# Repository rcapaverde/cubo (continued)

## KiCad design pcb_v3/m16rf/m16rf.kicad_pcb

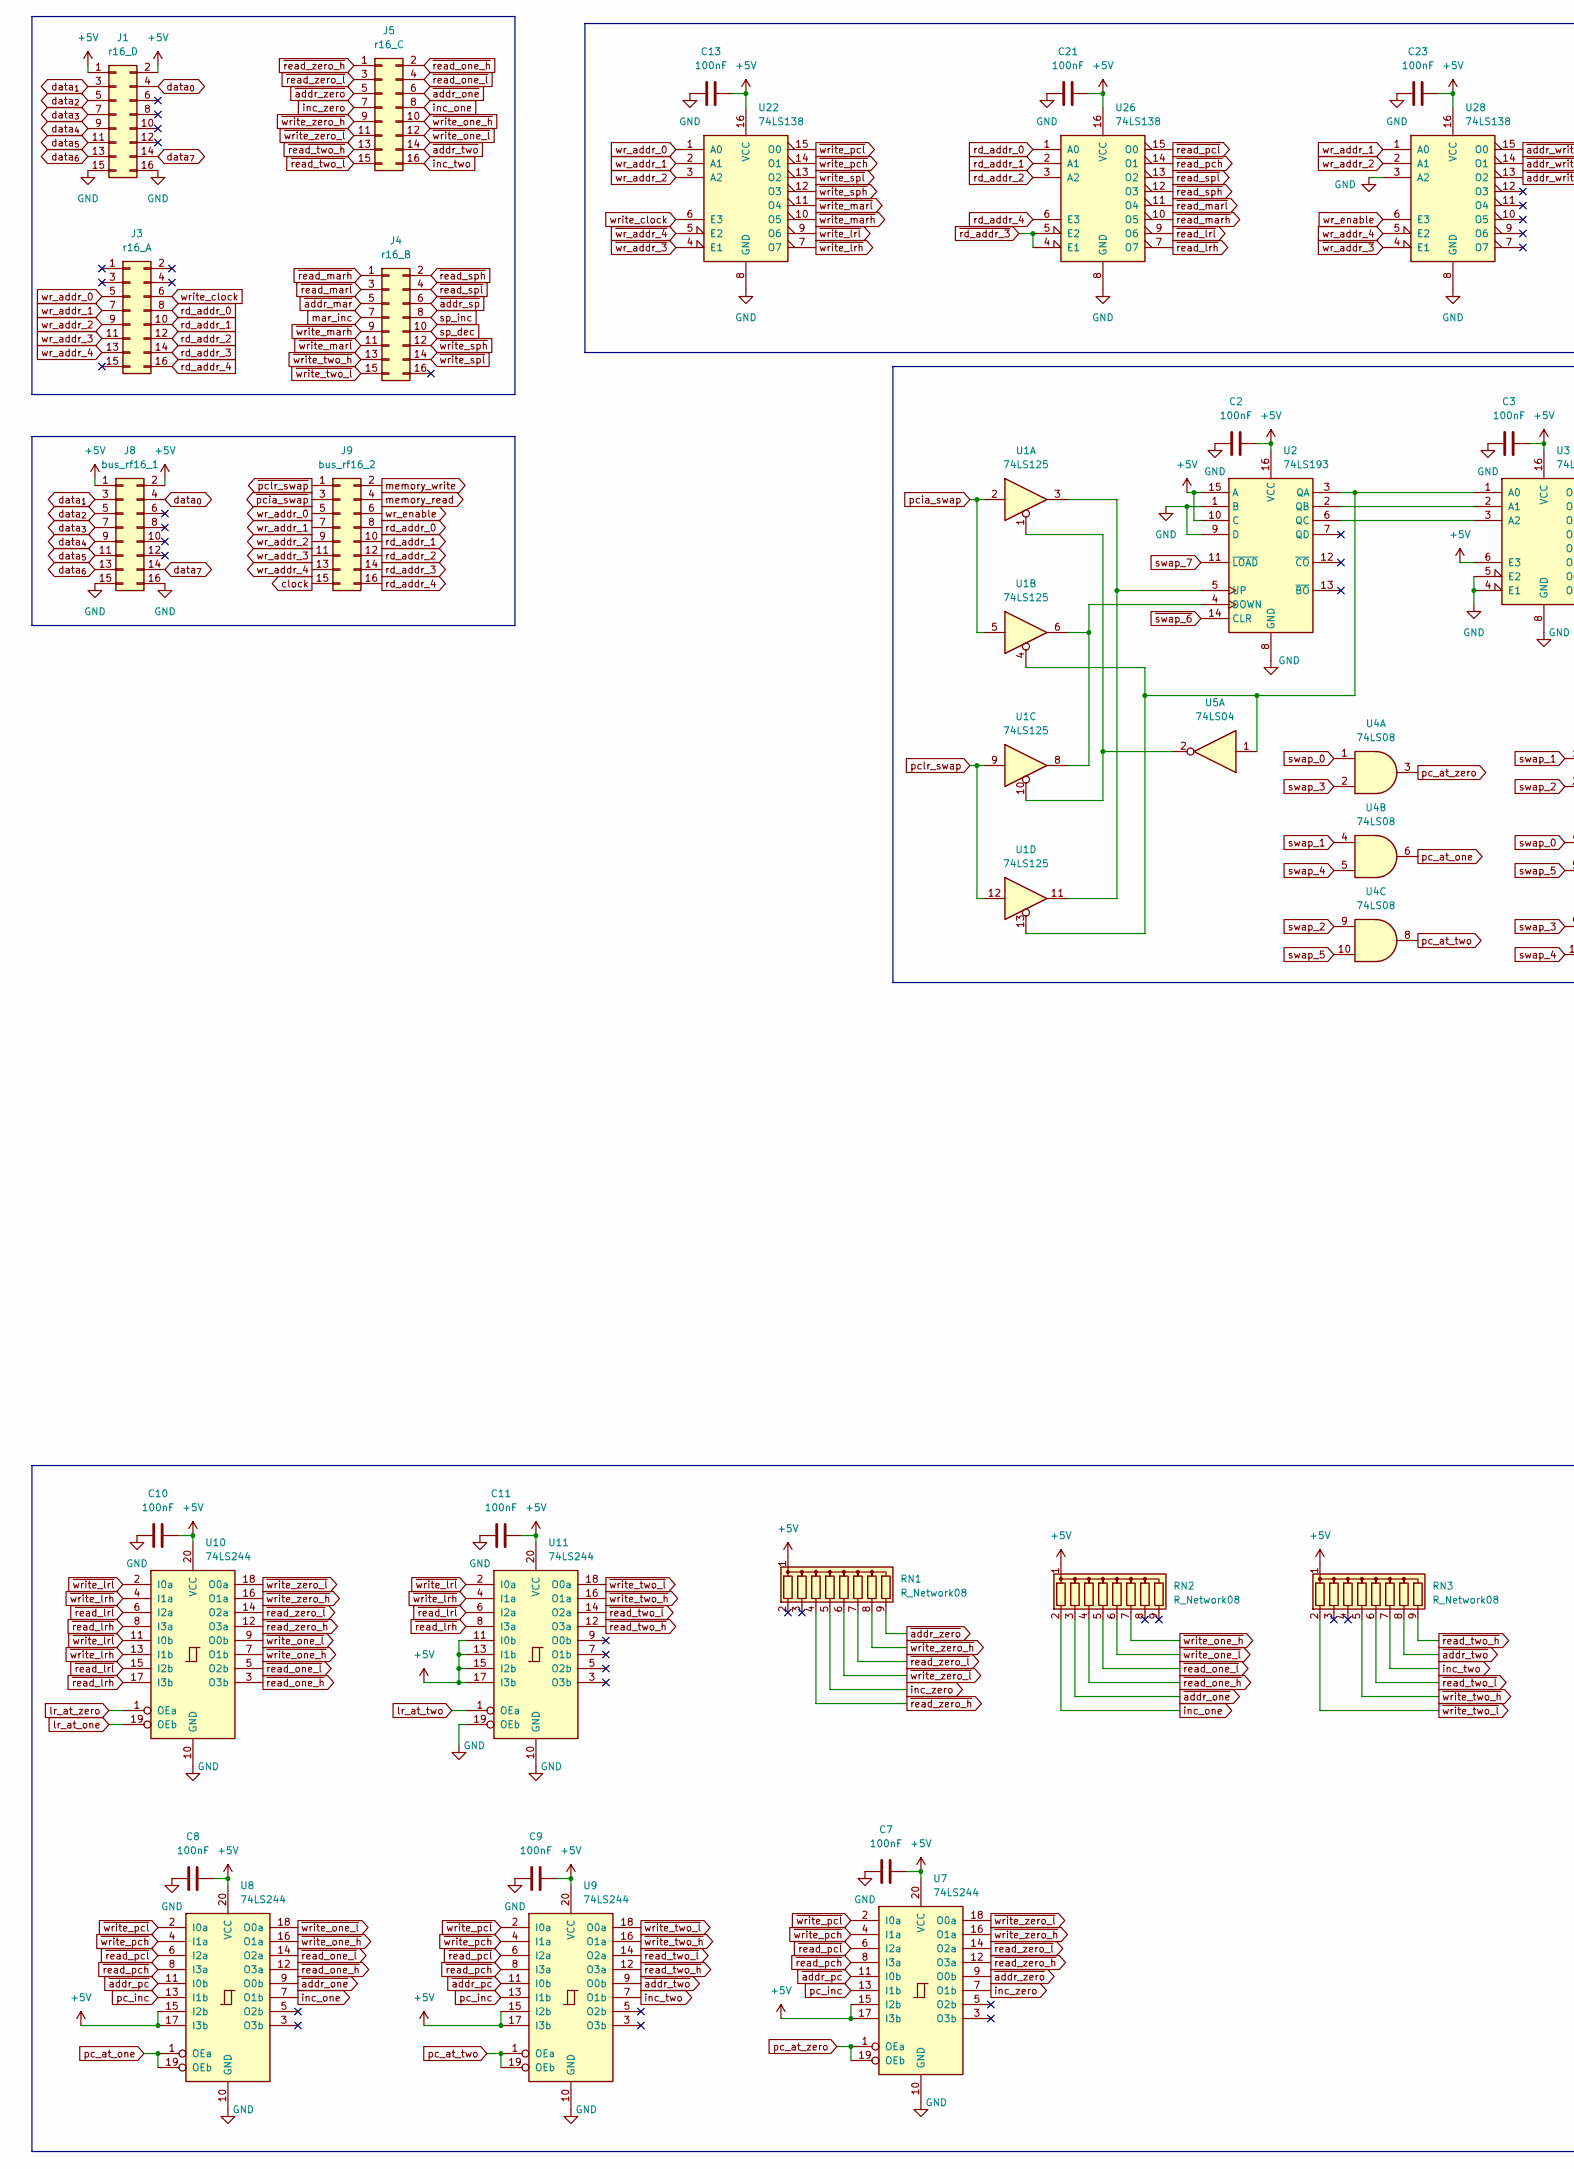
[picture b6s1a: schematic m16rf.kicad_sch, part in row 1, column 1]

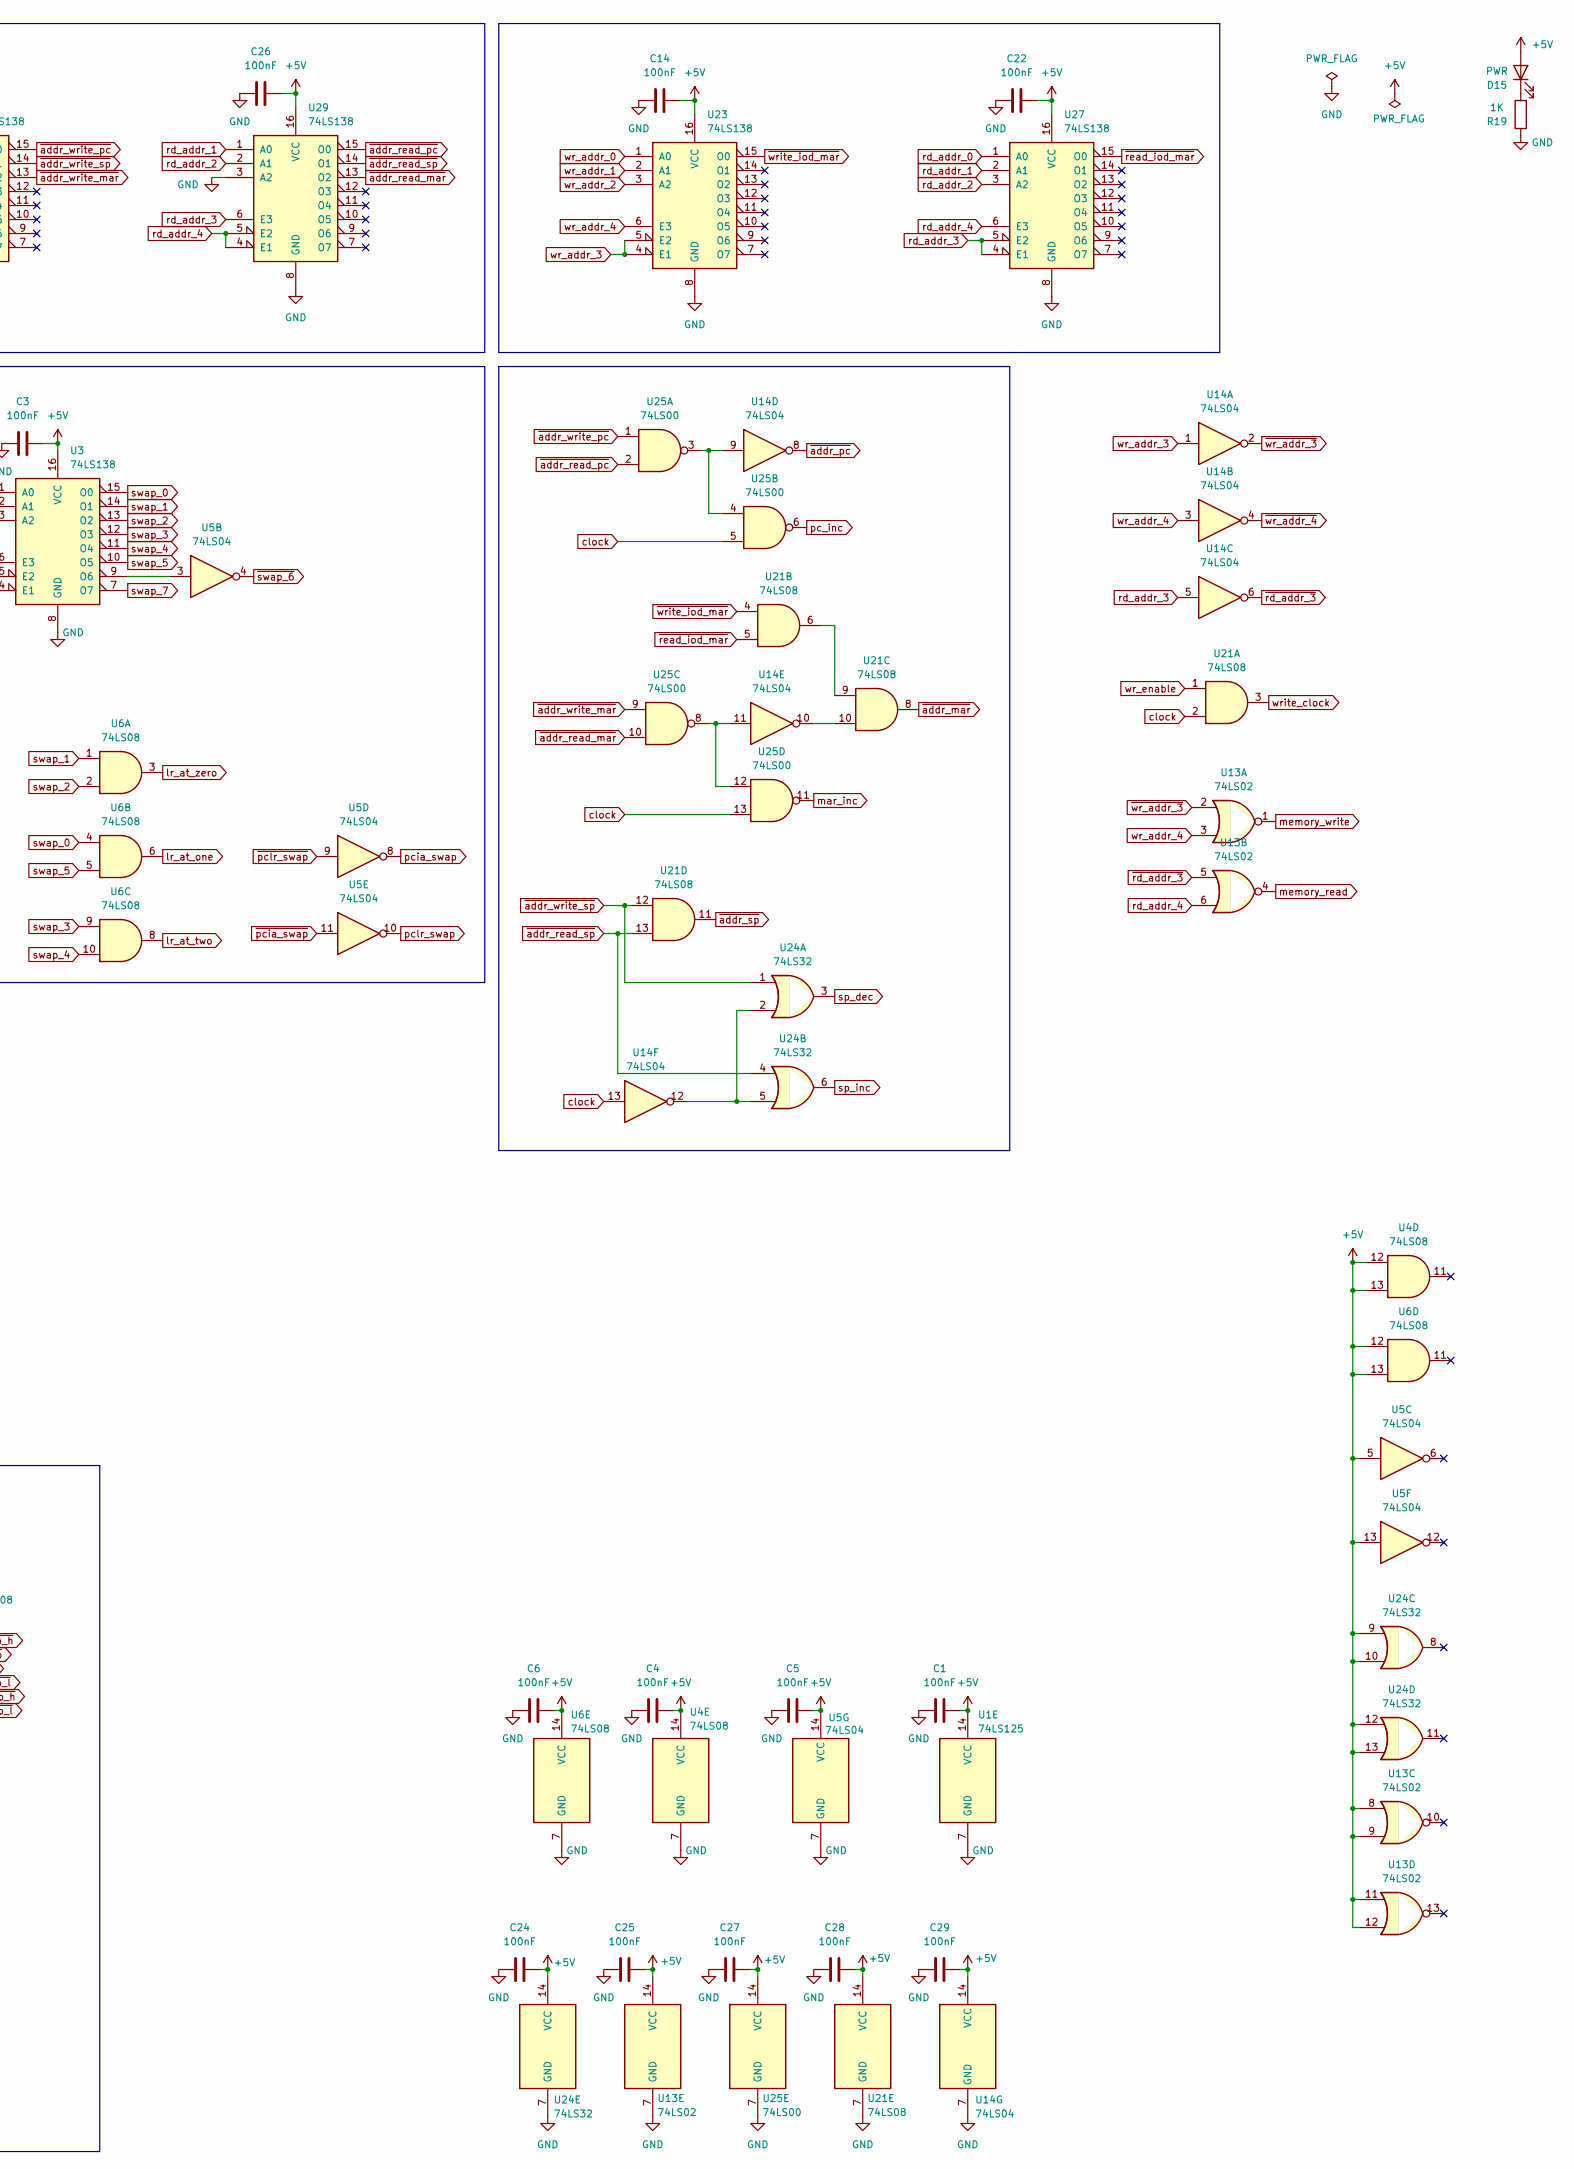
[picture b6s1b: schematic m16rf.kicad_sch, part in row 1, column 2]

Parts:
C1, C2, C3, C4, C5, C6, C7, C8, C9, C10, C11, C13, C14, C21, C22, C23, C24, C25, C26, C27, C28, C29: 100nF; C_Disc_D5.1mm_W3.2mm_P5.00mm
D15: PWR; LED_D5.0mm
J1: r16_D; conector 02x08
J3: r16_A; conector 02x08
J4: r16_B; conector 02x08
J5: r16_C; conector 02x08
J8: bus_rf16_1; conector 02x08
J9: bus_rf16_2; conector 02x08
R19: 1K; R_Axial_DIN0207_L6.3mm_D2.5mm_P7.62mm_Horizontal
RN1, RN2, RN3: R_Network08; R_Array_SIP9
U1: 74LS125; DIP-14_W7.62mm
U2: 74LS193; DIP-16_W7.62mm
U3, U22, U23, U26, U27, U28, U29: 74LS138; DIP-16_W7.62mm
U4, U6, U21: 74LS08; DIP-14_W7.62mm
U5, U14: 74LS04; DIP-14_W7.62mm
U7, U8, U9, U10, U11: 74LS244; DIP-20_W7.62mm
U13: 74LS02; DIP-14_W7.62mm
U24: 74LS32; DIP-14_W7.62mm
U25: 74LS00; DIP-14_W7.62mm

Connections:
+5V: C1.2, C2.2, C3.2, C4.2, C5.2, C6.2, C7.2, C8.2, C9.2, C10.2, C11.2, C13.2, C14.2, C21.2, C22.2, C23.2, C24.2, C25.2, C26.2, C27.2, C28.2, C29.2, D15.2 (A), J1.1, J1.2, J8.1, J8.2, RN1.1 (common), RN2.1 (common), RN3.1 (common), U1.14 (VCC), U2.10 (C), U2.15 (A), U2.16 (VCC), U3.6 (E3), U3.16 (VCC), U4.12, U4.13, U4.14 (VCC), U5.5, U5.13, U5.14 (VCC), U6.12, U6.13, U6.14 (VCC), U7.15 (I2b), U7.17 (I3b), U7.20 (VCC), U8.15 (I2b), U8.17 (I3b), U8.20 (VCC), U9.15 (I2b), U9.17 (I3b), U9.20 (VCC), U10.20 (VCC), U11.11 (I0b), U11.13 (I1b), U11.15 (I2b), U11.17 (I3b), U11.20 (VCC), U13.8, U13.9, U13.11, U13.12, U13.14 (VCC), U14.14 (VCC), U21.14 (VCC), U22.16 (VCC), U23.16 (VCC), U24.9, U24.10, U24.12, U24.13, U24.14 (VCC), U25.14 (VCC), U26.16 (VCC), U27.16 (VCC), U28.16 (VCC), U29.16 (VCC)
GND: C1.1, C2.1, C3.1, C4.1, C5.1, C6.1, C7.1, C8.1, C9.1, C10.1, C11.1, C13.1, C14.1, C21.1, C22.1, C23.1, C24.1, C25.1, C26.1, C27.1, C28.1, C29.1, J1.15, J1.16, J8.15, J8.16, R19.1, U1.7 (GND), U2.1 (B), U2.8 (GND), U2.9 (D), U3.4 (E1), U3.5 (E2), U3.8 (GND), U4.7 (GND), U5.7 (GND), U6.7 (GND), U7.10 (GND), U8.10 (GND), U9.10 (GND), U10.10 (GND), U11.10 (GND), U11.19 (OEb), U13.7 (GND), U14.7 (GND), U21.7 (GND), U22.8 (GND), U23.8 (GND), U24.7 (GND), U25.7 (GND), U26.8 (GND), U27.8 (GND), U28.3 (A2), U28.8 (GND), U29.3 (A2), U29.8 (GND)
unnamed: D15.1 (K), R19.2
unnamed: U1.1, U1.10, U5.2
unnamed: U1.6, U1.8, U2.4 (DOWN)
unnamed: U1.4, U1.13, U2.3 (QA), U3.1 (A0), U5.1
unnamed: U2.2 (QB), U3.2 (A1)
unnamed: U2.6 (QC), U3.3 (A2)
unnamed: U1.3, U1.11, U2.5 (UP)
unnamed: U3.9 (O6), U5.3
unnamed: U14.9, U25.3, U25.4
unnamed: U14.10, U21.10
unnamed: U14.11, U25.8, U25.12
unnamed: U14.12, U24.2, U24.5
unnamed: U21.6, U21.9
clock: J9.15, U14.13, U21.2, U25.5, U25.13
data_{0}: J1.4, J8.4
data_{1}: J1.3, J8.3
data_{2}: J1.5, J8.5
data_{3}: J1.7, J8.7
data_{4}: J1.9, J8.9
data_{5}: J1.11, J8.11
data_{6}: J1.13, J8.13
data_{7}: J1.14, J8.14
inc_one: J5.8, RN2.2 (R1), U8.7 (O1b)
inc_two: J5.16, RN3.7 (R6), U9.7 (O1b)
inc_zero: J5.7, RN1.5 (R4), U7.7 (O1b)
lr_at_one: U6.6, U10.19 (OEb)
lr_at_two: U6.8, U11.1 (OEa)
lr_at_zero: U6.3, U10.1 (OEa)
mar_inc: J4.7, U25.11
memory_read: J9.4, U13.4
memory_write: J9.2, U13.1
pc_at_one: U4.6, U8.1 (OEa), U8.19 (OEb)
pc_at_two: U4.8, U9.1 (OEa), U9.19 (OEb)
pc_at_zero: U4.3, U7.1 (OEa), U7.19 (OEb)
pc_inc: U7.13 (I1b), U8.13 (I1b), U9.13 (I1b), U25.6
pcia_swap: U1.2, U1.5, U5.8
pclr_swap: U1.9, U1.12, U5.10
rd_addr_0: J3.8, J9.8, U26.1 (A0), U27.1 (A0)
rd_addr_1: J3.10, J9.10, U26.2 (A1), U27.2 (A1), U29.1 (A0)
rd_addr_2: J3.12, J9.12, U26.3 (A2), U27.3 (A2), U29.2 (A1)
rd_addr_3: J3.14, J9.14, U14.5, U27.4 (E1), U27.5 (E2), U29.6 (E3)
rd_addr_4: J3.16, J9.16, U13.6, U26.6 (E3), U27.6 (E3), U29.4 (E1), U29.5 (E2)
sp_dec: J4.10, U24.3
sp_inc: J4.8, U24.6
swap_0: U3.15 (O0), U4.1, U6.4
swap_1: U3.14 (O1), U4.4, U6.1
swap_2: U3.13 (O2), U4.9, U6.2
swap_3: U3.12 (O3), U4.2, U6.9
swap_4: U3.11 (O4), U4.5, U6.10
swap_5: U3.10 (O5), U4.10, U6.5
swap_7: U2.11 (~LOAD), U3.7 (O7)
wr_addr_0: J3.5, J9.5, U22.1 (A0), U23.1 (A0)
wr_addr_1: J3.7, J9.7, U22.2 (A1), U23.2 (A1), U28.1 (A0)
wr_addr_2: J3.9, J9.9, U22.3 (A2), U23.3 (A2), U28.2 (A1)
wr_addr_3: J3.11, J9.11, U14.1, U23.4 (E1), U23.5 (E2)
wr_addr_4: J3.13, J9.13, U13.3, U14.3, U23.6 (E3), U28.5 (E2)
wr_enable: J9.6, U21.1, U28.6 (E3)
write_clock: J3.6, U21.3, U22.6 (E3)
~addr_mar: J4.5, U21.8
~addr_one: J5.6, RN2.3 (R2), U8.9 (O0b)
~addr_pc: U7.11 (I0b), U8.11 (I0b), U9.11 (I0b), U14.8
~addr_read_mar: U25.10, U29.13 (O2)
~addr_read_pc: U25.2, U29.15 (O0)
~addr_read_sp: U21.13, U24.4, U29.14 (O1)
~addr_sp: J4.6, U21.11
~addr_two: J5.14, RN3.8 (R7), U9.9 (O0b)
~addr_write_mar: U25.9, U28.13 (O2)
~addr_write_pc: U25.1, U28.15 (O0)
~addr_write_sp: U21.12, U24.1, U28.14 (O1)
~addr_zero: J5.5, RN1.9 (R8), U7.9 (O0b)
~pcia_swap: J9.3, U5.11
~pclr_swap: J9.1, U5.9
~rd_addr_3: U13.5, U14.6, U26.4 (E1), U26.5 (E2)
~read_iod_mar: U21.5, U27.15 (O0)
~read_lrh: U10.8 (I3a), U10.17 (I3b), U11.8 (I3a), U26.7 (O7)
~read_lrl: U10.6 (I2a), U10.15 (I2b), U11.6 (I2a), U26.9 (O6)
~read_marh: J4.1, U26.10 (O5)
~read_marl: J4.3, U26.11 (O4)
~read_one_h: J5.2, RN2.4 (R3), U8.12 (O3a), U10.3 (O3b)
~read_one_l: J5.4, RN2.5 (R4), U8.14 (O2a), U10.5 (O2b)
~read_pch: U7.8 (I3a), U8.8 (I3a), U9.8 (I3a), U26.14 (O1)
~read_pcl: U7.6 (I2a), U8.6 (I2a), U9.6 (I2a), U26.15 (O0)
~read_sph: J4.2, U26.12 (O3)
~read_spl: J4.4, U26.13 (O2)
~read_two_h: J5.13, RN3.9 (R8), U9.12 (O3a), U11.12 (O3a)
~read_two_l: J5.15, RN3.6 (R5), U9.14 (O2a), U11.14 (O2a)
~read_zero_h: J5.1, RN1.4 (R3), U7.12 (O3a), U10.12 (O3a)
~read_zero_l: J5.3, RN1.7 (R6), U7.14 (O2a), U10.14 (O2a)
~swap_6: U2.14 (CLR), U5.4
~wr_addr_3: U13.2, U14.2, U22.4 (E1), U28.4 (E1)
~wr_addr_4: U14.4, U22.5 (E2)
~write_iod_mar: U21.4, U23.15 (O0)
~write_lrh: U10.4 (I1a), U10.13 (I1b), U11.4 (I1a), U22.7 (O7)
~write_lrl: U10.2 (I0a), U10.11 (I0b), U11.2 (I0a), U22.9 (O6)
~write_marh: J4.9, U22.10 (O5)
~write_marl: J4.11, U22.11 (O4)
~write_one_h: J5.10, RN2.7 (R6), U8.16 (O1a), U10.7 (O1b)
~write_one_l: J5.12, RN2.6 (R5), U8.18 (O0a), U10.9 (O0b)
~write_pch: U7.4 (I1a), U8.4 (I1a), U9.4 (I1a), U22.14 (O1)
~write_pcl: U7.2 (I0a), U8.2 (I0a), U9.2 (I0a), U22.15 (O0)
~write_sph: J4.12, U22.12 (O3)
~write_spl: J4.14, U22.13 (O2)
~write_two_h: J4.13, RN3.5 (R4), U9.16 (O1a), U11.16 (O1a)
~write_two_l: J4.15, RN3.2 (R1), U9.18 (O0a), U11.18 (O0a)
~write_zero_h: J5.9, RN1.8 (R7), U7.16 (O1a), U10.16 (O1a)
~write_zero_l: J5.11, RN1.6 (R5), U7.18 (O0a), U10.18 (O0a)

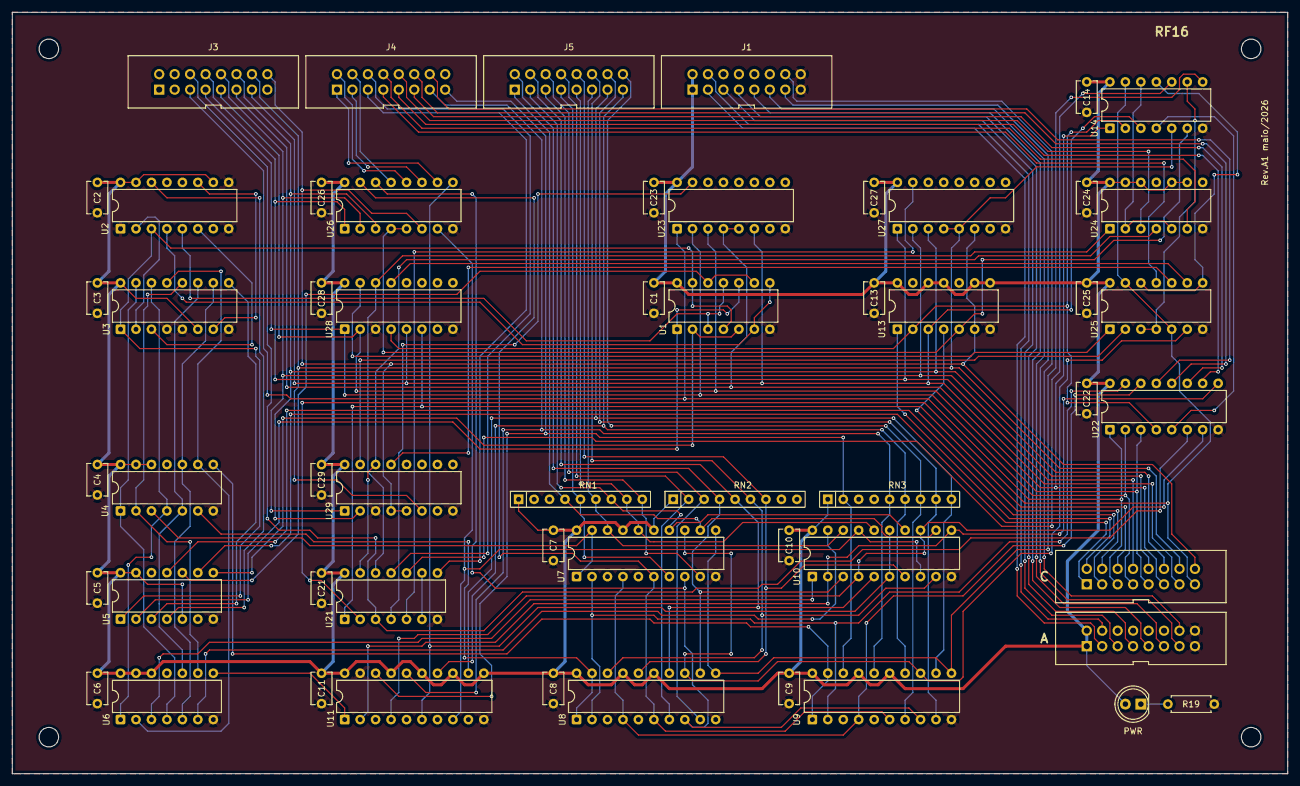
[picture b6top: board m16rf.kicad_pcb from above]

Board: 2 copper layers, 209.5 x 125.1 mm, 55 parts (0 on the bottom side), 108 nets.

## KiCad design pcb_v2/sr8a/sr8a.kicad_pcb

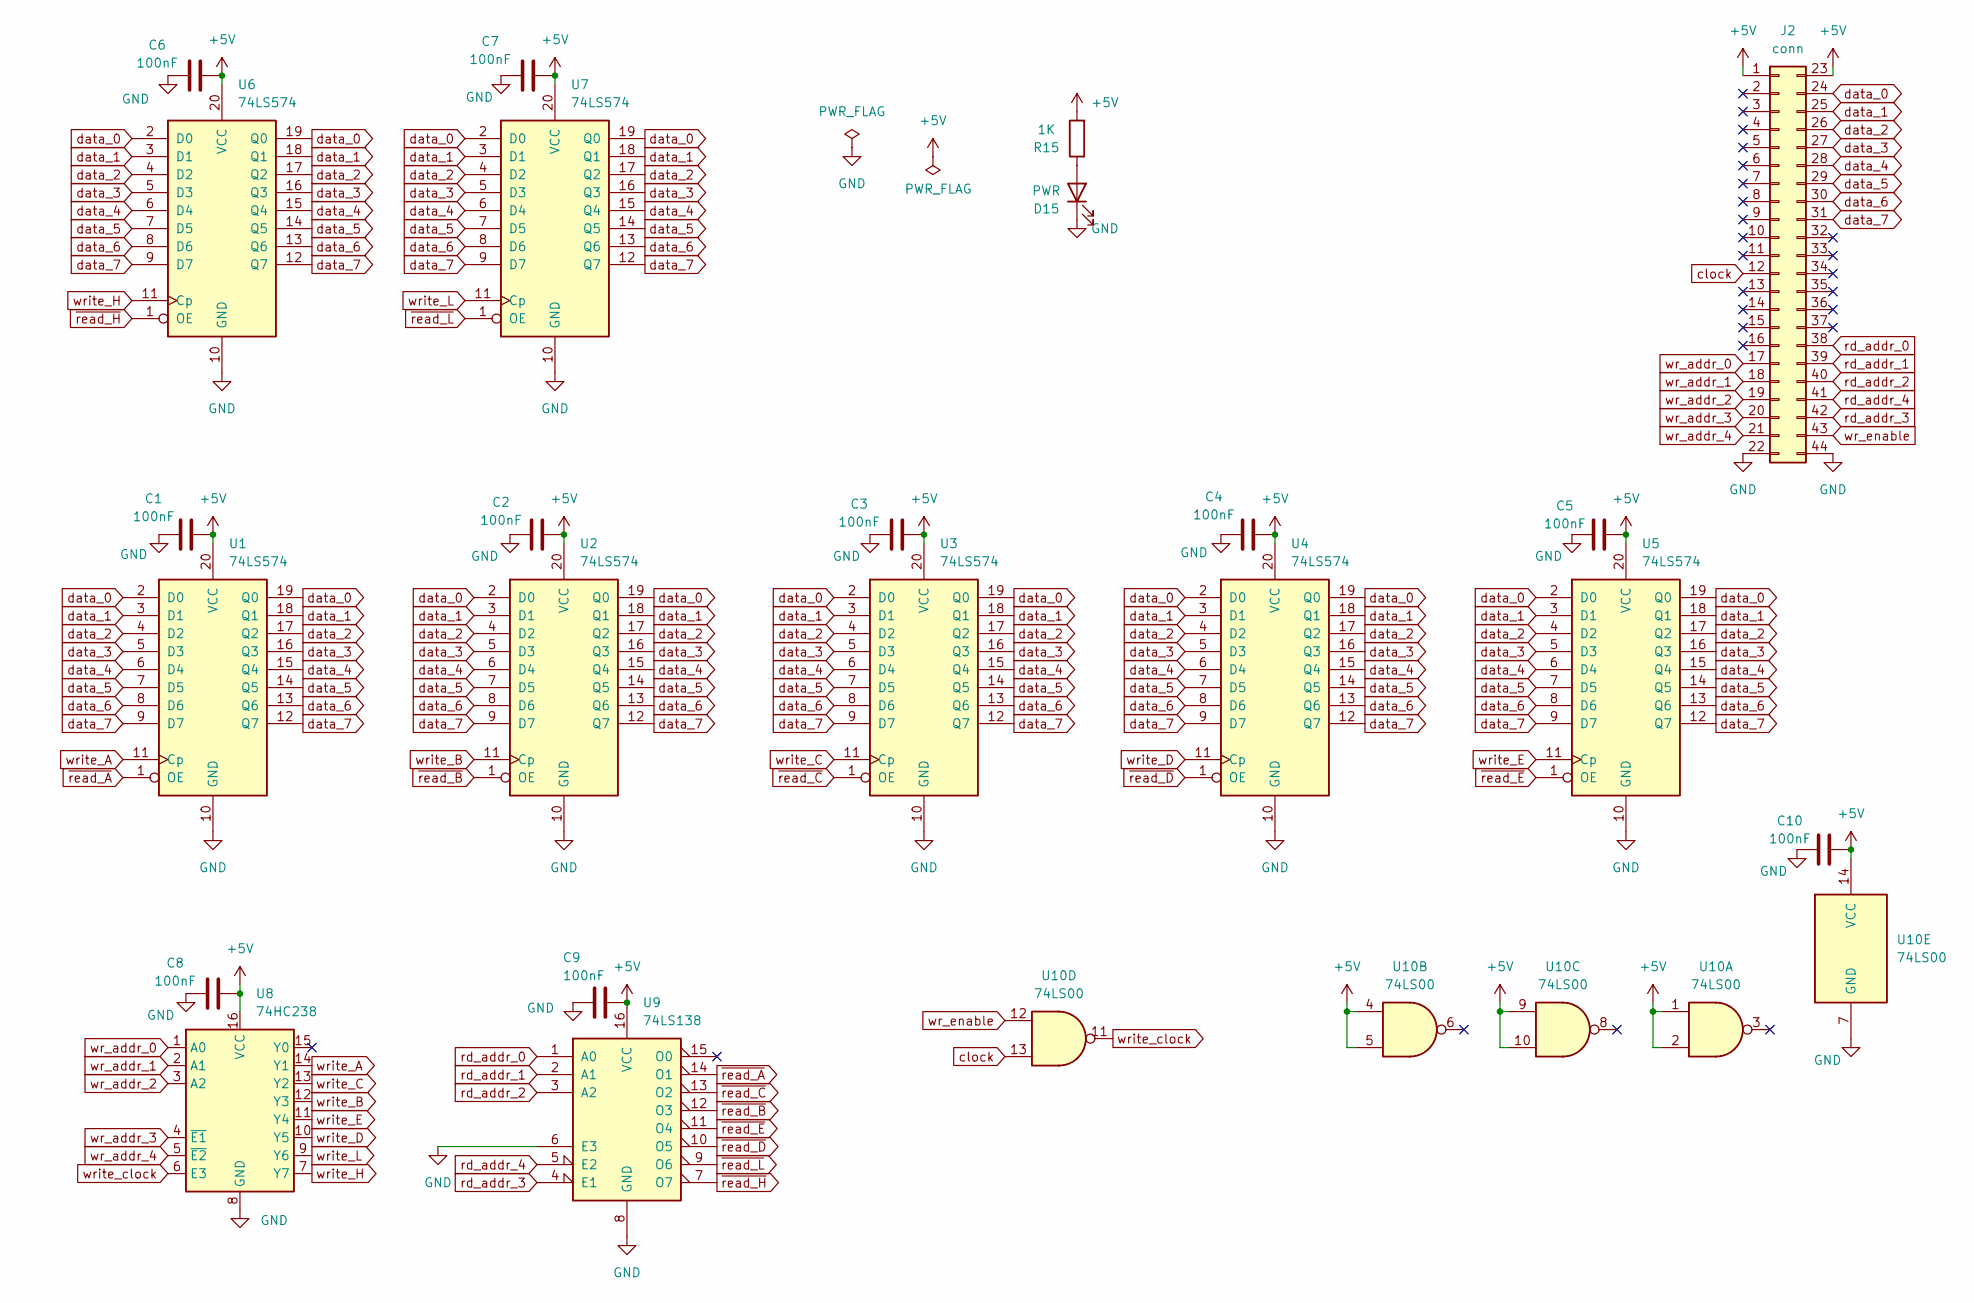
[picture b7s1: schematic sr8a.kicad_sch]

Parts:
C1, C2, C3, C4, C5, C6, C7, C8, C9, C10: 100nF; C_Disc_D5.1mm_W3.2mm_P5.00mm
D15: PWR; LED_D5.0mm
J2: conn; edge-connector-44
R15: 1K; R_Axial_DIN0207_L6.3mm_D2.5mm_P7.62mm_Horizontal
U1, U2, U3, U4, U5, U6, U7: 74LS574; DIP-20_W7.62mm
U8: 74HC238; DIP-16_W7.62mm
U9: 74LS138; DIP-16_W7.62mm
U10: 74LS00; DIP-14_W7.62mm

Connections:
+5V: C1.2, C2.2, C3.2, C4.2, C5.2, C6.2, C7.2, C8.2, C9.2, C10.2, J2.1, J2.23, R15.2, U1.20 (VCC), U2.20 (VCC), U3.20 (VCC), U4.20 (VCC), U5.20 (VCC), U6.20 (VCC), U7.20 (VCC), U8.16 (VCC), U9.16 (VCC), U10.1, U10.2, U10.4, U10.5, U10.9, U10.10, U10.14 (VCC)
GND: C1.1, C2.1, C3.1, C4.1, C5.1, C6.1, C7.1, C8.1, C9.1, C10.1, D15.1 (K), J2.22, J2.44, U1.10 (GND), U2.10 (GND), U3.10 (GND), U4.10 (GND), U5.10 (GND), U6.10 (GND), U7.10 (GND), U8.8 (GND), U9.6 (E3), U9.8 (GND), U10.7 (GND)
unnamed: D15.2 (A), R15.1
clock: J2.12, U10.13
data_0: J2.24, U1.2 (D0), U1.19 (Q0), U2.2 (D0), U2.19 (Q0), U3.2 (D0), U3.19 (Q0), U4.2 (D0), U4.19 (Q0), U5.2 (D0), U5.19 (Q0), U6.2 (D0), U6.19 (Q0), U7.2 (D0), U7.19 (Q0)
data_1: J2.25, U1.3 (D1), U1.18 (Q1), U2.3 (D1), U2.18 (Q1), U3.3 (D1), U3.18 (Q1), U4.3 (D1), U4.18 (Q1), U5.3 (D1), U5.18 (Q1), U6.3 (D1), U6.18 (Q1), U7.3 (D1), U7.18 (Q1)
data_2: J2.26, U1.4 (D2), U1.17 (Q2), U2.4 (D2), U2.17 (Q2), U3.4 (D2), U3.17 (Q2), U4.4 (D2), U4.17 (Q2), U5.4 (D2), U5.17 (Q2), U6.4 (D2), U6.17 (Q2), U7.4 (D2), U7.17 (Q2)
data_3: J2.27, U1.5 (D3), U1.16 (Q3), U2.5 (D3), U2.16 (Q3), U3.5 (D3), U3.16 (Q3), U4.5 (D3), U4.16 (Q3), U5.5 (D3), U5.16 (Q3), U6.5 (D3), U6.16 (Q3), U7.5 (D3), U7.16 (Q3)
data_4: J2.28, U1.6 (D4), U1.15 (Q4), U2.6 (D4), U2.15 (Q4), U3.6 (D4), U3.15 (Q4), U4.6 (D4), U4.15 (Q4), U5.6 (D4), U5.15 (Q4), U6.6 (D4), U6.15 (Q4), U7.6 (D4), U7.15 (Q4)
data_5: J2.29, U1.7 (D5), U1.14 (Q5), U2.7 (D5), U2.14 (Q5), U3.7 (D5), U3.14 (Q5), U4.7 (D5), U4.14 (Q5), U5.7 (D5), U5.14 (Q5), U6.7 (D5), U6.14 (Q5), U7.7 (D5), U7.14 (Q5)
data_6: J2.30, U1.8 (D6), U1.13 (Q6), U2.8 (D6), U2.13 (Q6), U3.8 (D6), U3.13 (Q6), U4.8 (D6), U4.13 (Q6), U5.8 (D6), U5.13 (Q6), U6.8 (D6), U6.13 (Q6), U7.8 (D6), U7.13 (Q6)
data_7: J2.31, U1.9 (D7), U1.12 (Q7), U2.9 (D7), U2.12 (Q7), U3.9 (D7), U3.12 (Q7), U4.9 (D7), U4.12 (Q7), U5.9 (D7), U5.12 (Q7), U6.9 (D7), U6.12 (Q7), U7.9 (D7), U7.12 (Q7)
rd_addr_0: J2.38, U9.1 (A0)
rd_addr_1: J2.39, U9.2 (A1)
rd_addr_2: J2.40, U9.3 (A2)
rd_addr_3: J2.42, U9.4 (E1)
rd_addr_4: J2.41, U9.5 (E2)
wr_addr_0: J2.17, U8.1 (A0)
wr_addr_1: J2.18, U8.2 (A1)
wr_addr_2: J2.19, U8.3 (A2)
wr_addr_3: J2.20, U8.4 (~E1)
wr_addr_4: J2.21, U8.5 (~E2)
wr_enable: J2.43, U10.12
write_A: U1.11 (Cp), U8.14 (Y1)
write_B: U2.11 (Cp), U8.12 (Y3)
write_C: U3.11 (Cp), U8.13 (Y2)
write_D: U4.11 (Cp), U8.10 (Y5)
write_E: U5.11 (Cp), U8.11 (Y4)
write_H: U6.11 (Cp), U8.7 (Y7)
write_L: U7.11 (Cp), U8.9 (Y6)
write_clock: U8.6 (E3), U10.11
~read_A: U1.1 (OE), U9.14 (O1)
~read_B: U2.1 (OE), U9.12 (O3)
~read_C: U3.1 (OE), U9.13 (O2)
~read_D: U4.1 (OE), U9.10 (O5)
~read_E: U5.1 (OE), U9.11 (O4)
~read_H: U6.1 (OE), U9.7 (O7)
~read_L: U7.1 (OE), U9.9 (O6)

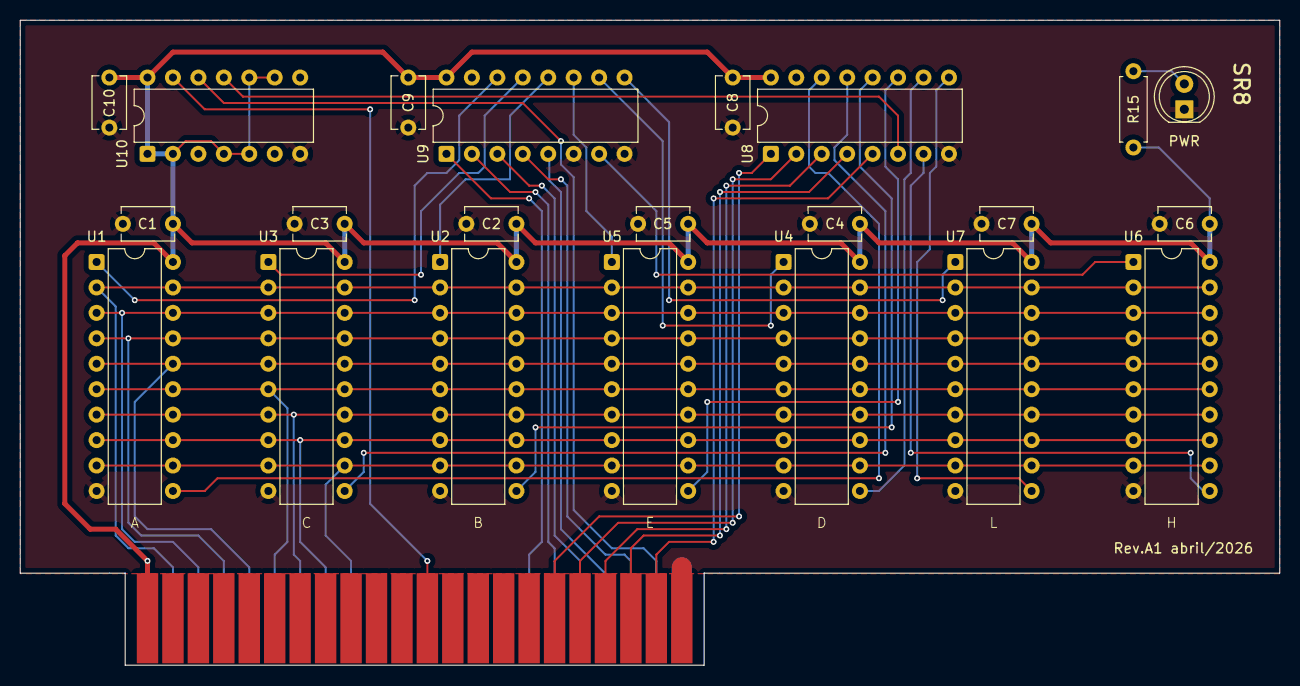
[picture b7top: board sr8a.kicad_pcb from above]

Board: 2 copper layers, 125.7 x 64.4 mm, 23 parts (0 on the bottom side), 38 nets.

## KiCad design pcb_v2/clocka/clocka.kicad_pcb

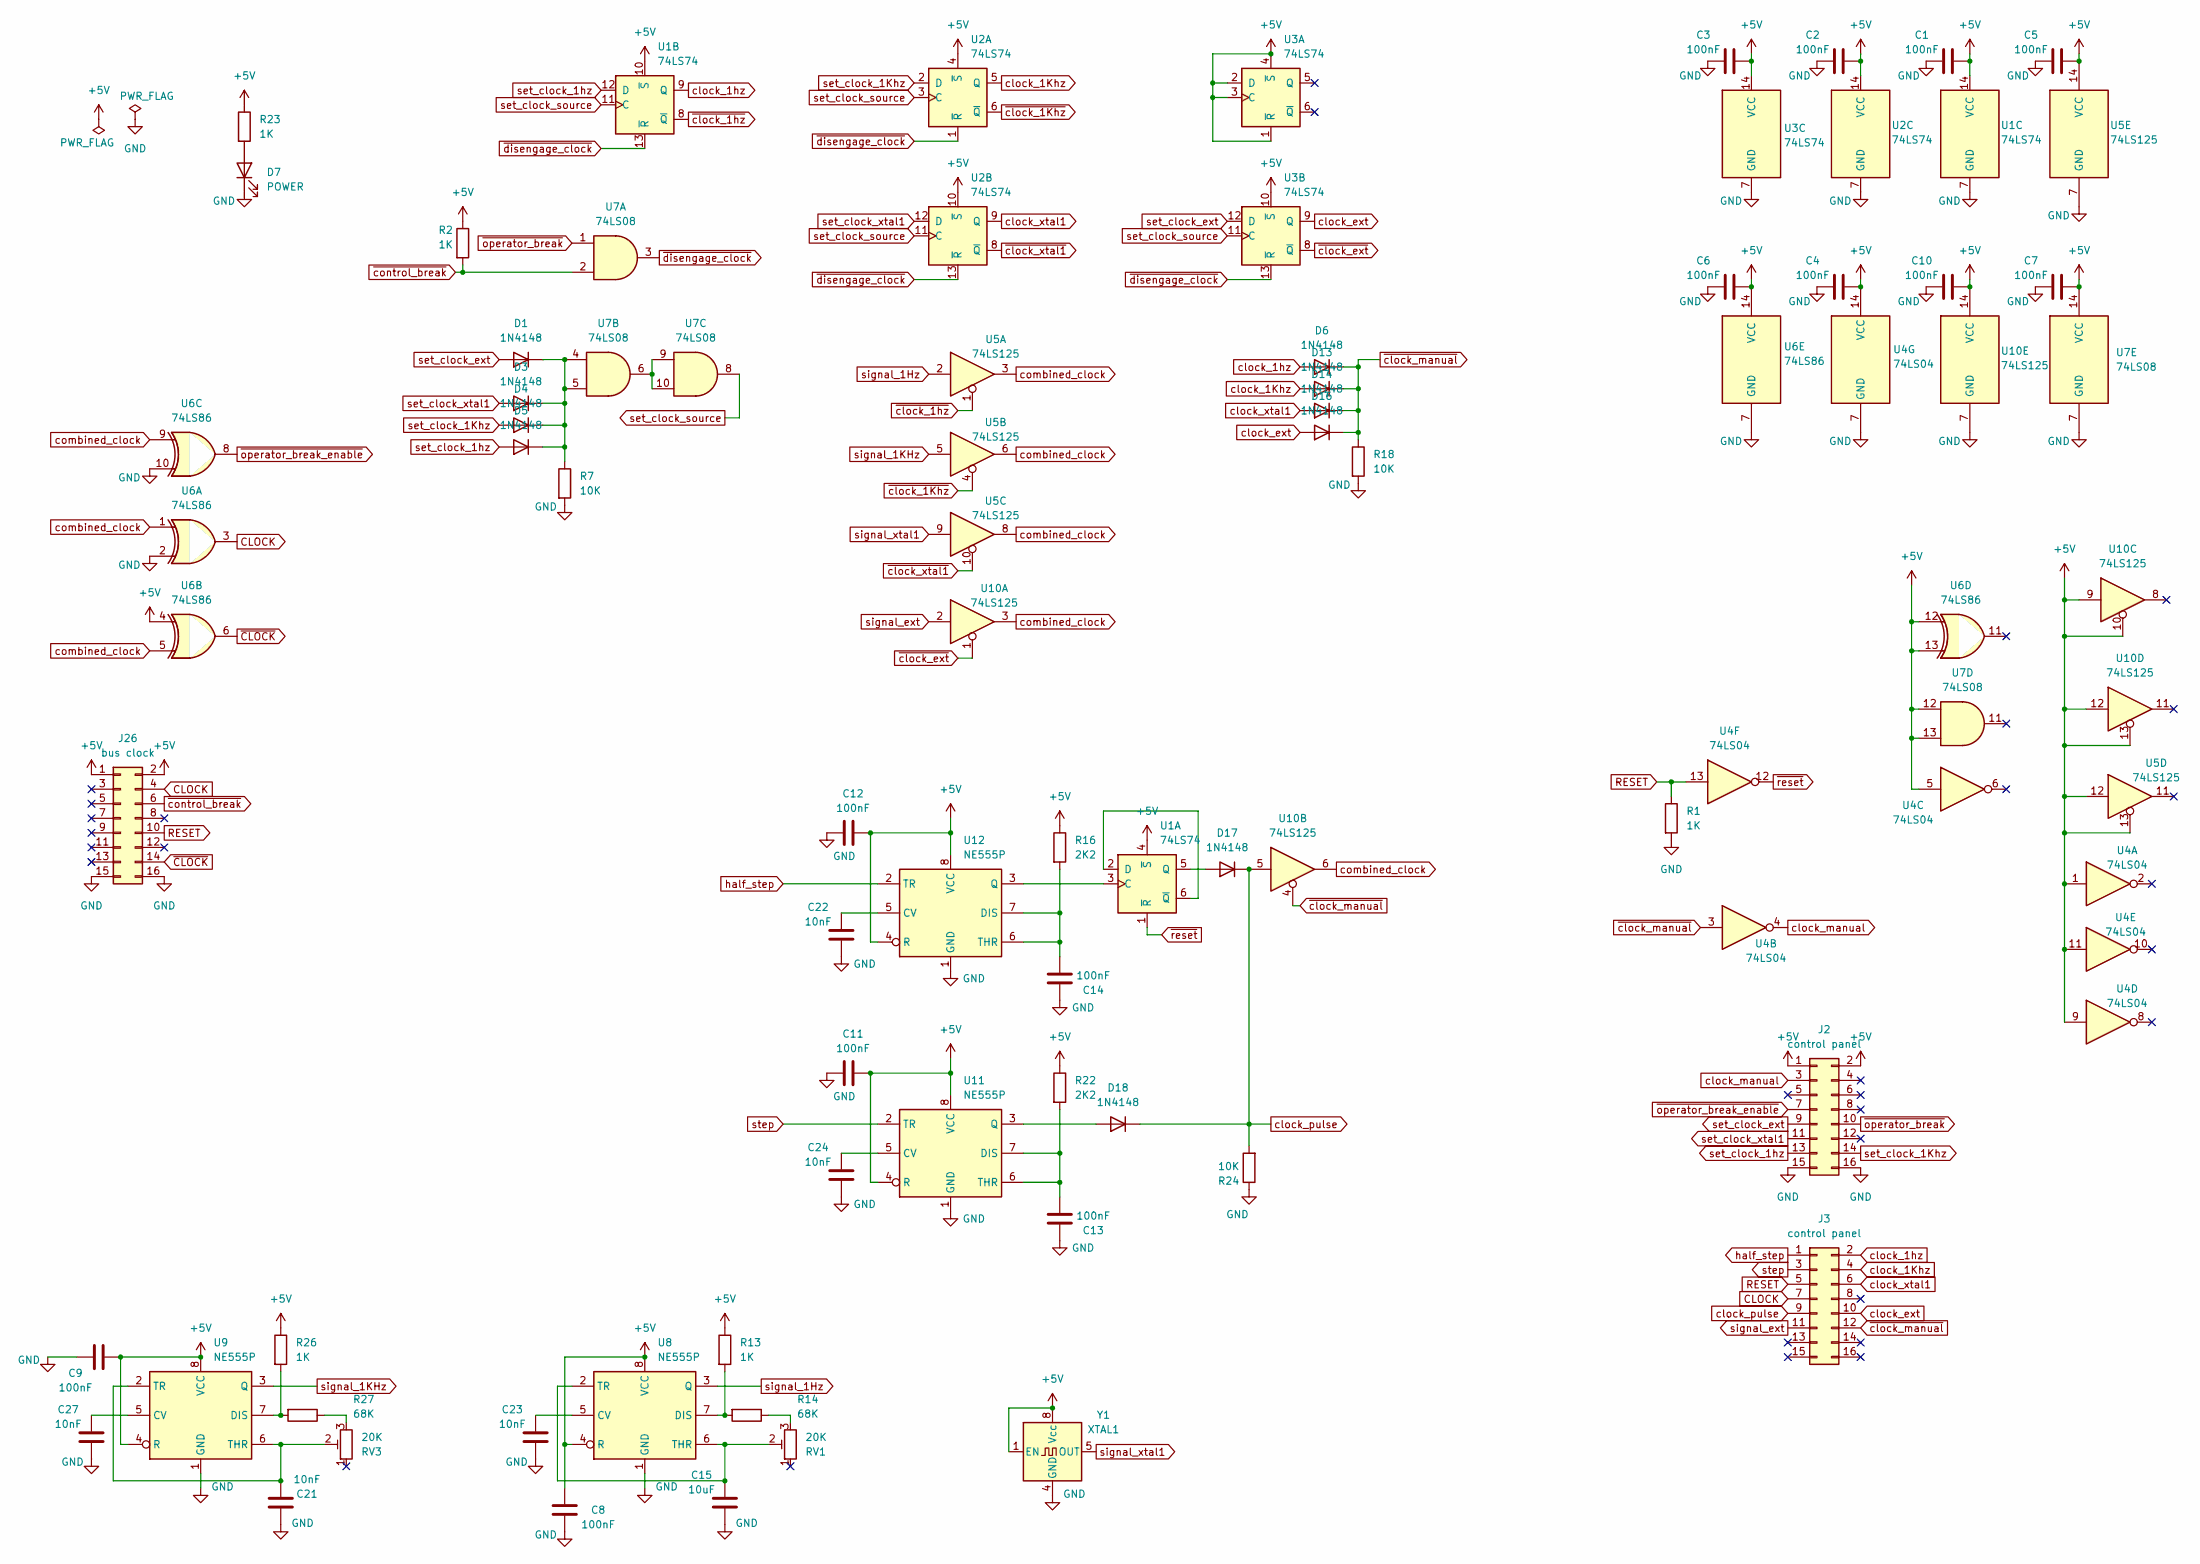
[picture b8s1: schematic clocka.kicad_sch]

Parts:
C1, C2, C3, C4, C5, C6, C7, C8, C9, C10, C11, C12, C13, C14: 100nF; C_Disc_D4.7mm_W2.5mm_P5.00mm
C15: 10uF; C_Disc_D4.7mm_W2.5mm_P5.00mm
C21, C22, C23, C24, C27: 10nF; C_Disc_D4.7mm_W2.5mm_P5.00mm
D1, D3, D4, D5, D6, D13, D14, D16, D17, D18: 1N4148; D_DO-35_SOD27_P7.62mm_Horizontal
D7: POWER; LED_D5.0mm
J2, J3: control panel; PinHeader_2x08_P2.54mm_Vertical
J26: bus clock; PinHeader_2x08_P2.54mm_Vertical
R1, R2, R13, R23, R26: 1K; R_Axial_DIN0207_L6.3mm_D2.5mm_P7.62mm_Horizontal
R7, R18, R24: 10K; R_Axial_DIN0207_L6.3mm_D2.5mm_P7.62mm_Horizontal
R14, R27: 68K; R_Axial_DIN0207_L6.3mm_D2.5mm_P7.62mm_Horizontal
R16, R22: 2K2; R_Axial_DIN0207_L6.3mm_D2.5mm_P7.62mm_Horizontal
RV1, RV3: 20K; Potentiometer_ACP_CA9-H5_Horizontal
U1, U2, U3: 74LS74; DIP-14_W7.62mm
U4: 74LS04; DIP-14_W7.62mm
U5, U10: 74LS125; DIP-14_W7.62mm
U6: 74LS86; DIP-14_W7.62mm
U7: 74LS08; DIP-14_W7.62mm
U8, U9, U11, U12: NE555P; DIP-8_W7.62mm
Y1: XTAL1; Oscillator_DIP-8

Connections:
+5V: C1.2, C2.2, C3.2, C4.2, C5.2, C6.2, C7.2, C8.1, C9.1, C10.2, C11.2, C12.2, J2.1, J2.2, J26.1, J26.2, R2.1, R13.1, R16.1, R22.1, R23.1, R26.1, U1.4 (~S), U1.10 (~S), U1.14 (VCC), U2.4 (~S), U2.10 (~S), U2.14 (VCC), U3.1 (~R), U3.2 (D), U3.3 (C), U3.4 (~S), U3.10 (~S), U3.14 (VCC), U4.1, U4.5, U4.9, U4.11, U4.14 (VCC), U5.12, U5.13, U5.14 (VCC), U6.4, U6.12, U6.13, U6.14 (VCC), U7.12, U7.13, U7.14 (VCC), U8.4 (R), U8.8 (VCC), U9.4 (R), U9.8 (VCC), U10.9, U10.10, U10.12, U10.13, U10.14 (VCC), U11.4 (R), U11.8 (VCC), U12.4 (R), U12.8 (VCC), Y1.1 (EN), Y1.8 (Vcc)
CLOCK: J3.7, J26.4, U6.3
GND: C1.1, C2.1, C3.1, C4.1, C5.1, C6.1, C7.1, C8.2, C9.2, C10.1, C11.1, C12.1, C13.1, C14.1, C15.1, C21.1, C22.1, C23.1, C24.1, C27.1, D7.1 (K), J2.15, J2.16, J26.15, J26.16, R1.2, R7.2, R18.2, R24.1, U1.7 (GND), U2.7 (GND), U3.7 (GND), U4.7 (GND), U5.7 (GND), U6.2, U6.7 (GND), U6.10, U7.7 (GND), U8.1 (GND), U9.1 (GND), U10.7 (GND), U11.1 (GND), U12.1 (GND), Y1.4 (GND)
unnamed: D1.1 (K), D3.1 (K), D4.1 (K), D5.1 (K), R7.1, U7.4, U7.5
unnamed: D7.2 (A), R23.2
unnamed: D17.2 (A), U1.5 (Q)
unnamed: D18.2 (A), U11.3 (Q)
unnamed: R14.1, RV1.3
unnamed: R27.1, RV3.3
unnamed: U1.2 (D), U1.6 (~Q)
unnamed: U7.6, U7.9, U7.10
unnamed: C23.2, U8.5 (CV)
unnamed: R13.2, R14.2, U8.7 (DIS)
unnamed: C15.2, RV1.2, U8.2 (TR), U8.6 (THR)
unnamed: C27.2, U9.5 (CV)
unnamed: R26.2, R27.2, U9.7 (DIS)
unnamed: C21.2, RV3.2, U9.2 (TR), U9.6 (THR)
unnamed: C24.2, U11.5 (CV)
unnamed: C13.2, R22.2, U11.6 (THR), U11.7 (DIS)
unnamed: C22.2, U12.5 (CV)
unnamed: C14.2, R16.2, U12.6 (THR), U12.7 (DIS)
unnamed: U1.3 (C), U12.3 (Q)
RESET: J3.5, J26.10, R1.1, U4.13
clock_1Khz: D13.2 (A), J3.4, U2.5 (Q)
clock_1hz: D6.2 (A), J3.2, U1.9 (Q)
clock_ext: D16.2 (A), J3.10, U3.9 (Q)
clock_manual: J2.3, U4.4
clock_pulse: D17.1 (K), D18.1 (K), J3.9, R24.2, U10.5
clock_xtal1: D14.2 (A), J3.6, U2.9 (Q)
combined_clock: U5.3, U5.6, U5.8, U6.1, U6.5, U6.9, U10.3, U10.6
half_step: J3.1, U12.2 (TR)
set_clock_1Khz: D4.2 (A), J2.14, U2.2 (D)
set_clock_1hz: D5.2 (A), J2.13, U1.12 (D)
set_clock_ext: D1.2 (A), J2.9, U3.12 (D)
set_clock_source: U1.11 (C), U2.3 (C), U2.11 (C), U3.11 (C), U7.8
set_clock_xtal1: D3.2 (A), J2.11, U2.12 (D)
signal_1Hz: U5.2, U8.3 (Q)
signal_1KHz: U5.5, U9.3 (Q)
signal_ext: J3.11, U10.2
signal_xtal1: U5.9, Y1.5 (OUT)
step: J3.3, U11.2 (TR)
~CLOCK: J26.14, U6.6
~clock_1Khz: U2.6 (~Q), U5.4
~clock_1hz: U1.8 (~Q), U5.1
~clock_ext: U3.8 (~Q), U10.1
~clock_manual: D6.1 (K), D13.1 (K), D14.1 (K), D16.1 (K), J3.12, R18.1, U4.3, U10.4
~clock_xtal1: U2.8 (~Q), U5.10
~control_break: J26.6, R2.2, U7.2
~disengage_clock: U1.13 (~R), U2.1 (~R), U2.13 (~R), U3.13 (~R), U7.3
~operator_break_enable: J2.7, U6.8
~operator_break: J2.10, U7.1
~reset: U1.1 (~R), U4.12
